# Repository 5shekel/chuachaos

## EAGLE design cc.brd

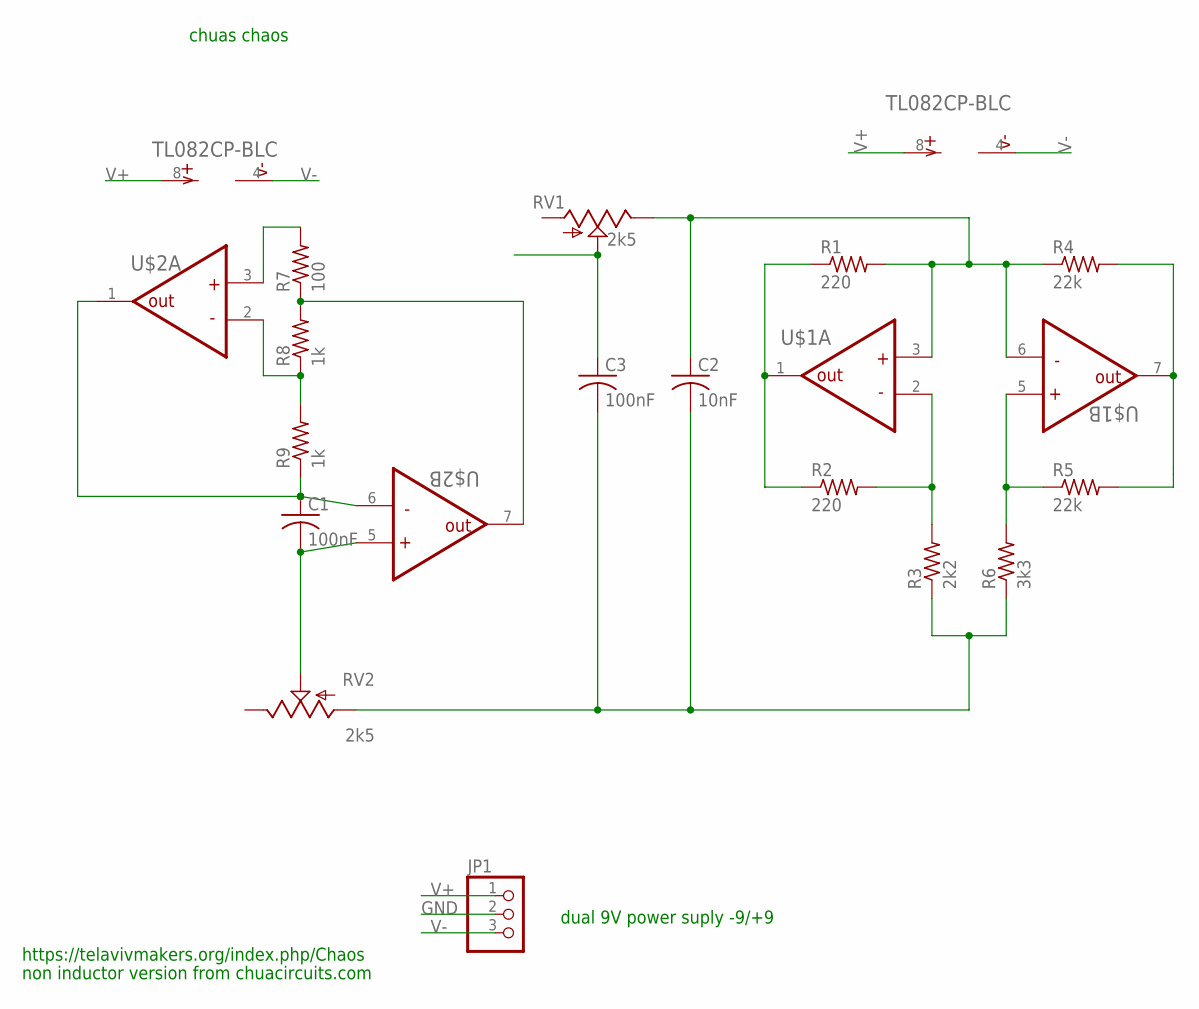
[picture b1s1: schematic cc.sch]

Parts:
C1, C3: 100nF; C025-024X044
C2: 10nF; C025-024X044
JP1: PINHD-1X3; 1X03
R1, R2: 220; 0204/5
R3: 2k2; 0204/5
R4, R5: 22k; 0204/5
R6: 3k3; 0204/5
R7: 100; 0204/5
R8, R9: 1k; 0204/5
RV1, RV2: 2k5; POT_ALPHA_RV16AF-20
U$1, U$2: TL082CP-BLC; DIP254P762X508-8

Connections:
GND: JP1.2
unnamed: R4.2, R5.2, U$1.7 (OUT)
unnamed: R5.1, R6.2, U$1.5 (+)
unnamed: R7.1, R8.2, U$2.7 (OUT)
unnamed: C2.1, R1.2, R4.1, RV1.3 (E), U$1.3 (+), U$1.6 (-)
unnamed: R2.2, R3.2, U$1.2 (-)
unnamed: R1.1, R2.1, U$1.1 (OUT)
unnamed: C2.2, C3.2, R3.1, R6.1, RV2.1 (A)
unnamed: C3.1, RV1.2 (S)
unnamed: R8.1, R9.2, U$2.2 (-)
unnamed: R7.2, U$2.3 (+)
unnamed: C1.1, R9.1, U$2.1 (OUT), U$2.6 (-)
unnamed: C1.2, RV2.2 (S), U$2.5 (+)
V+: JP1.1, U$1.8, U$2.8
V-: JP1.3, U$1.4, U$2.4

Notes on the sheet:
chuas chaos
non inductor version from chuacircuits.com
dual 9V power suply -9/+9
https://telavivmakers.org/index.php/Chaos

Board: 2 copper layers, 17 parts (0 on the bottom side), 14 nets, no tracks yet.

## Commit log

2017-04-14 circuit and lib

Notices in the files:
parts and their libraries:
SparkFun-Electromechanical: Licensing: Creative Commons ShareAlike 4.0 International - https://creativecommons.org/licenses/by-sa/4.0
